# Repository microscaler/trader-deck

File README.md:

# PriceWhisperer Deck, rev A: case and board files

## 3D concept
The original concept is in [`concept/index.html`](concept/index.html). Open it in a browser to rotate it, tap keys, arm live orders and flip the FLATTEN guard. It loads three.js from a CDN, so it needs a network connection.

The concept is the design intent, not the built geometry. The case and board below differ from it in the ways listed under "What changed from the 3D concept".

## Layout
| Path | Contents |
|---|---|
| `src/` | Python that generates everything: `geom.py` (dimensions), `board.py` (footprints and nets), `route.py`, `fab.py`, `kicad.py`, `stl.py` |
| `gerber/` | Fabrication set: Gerbers, drill files, BOM |
| `stl/` | Printable case parts |
| `kicad/` | The routed board as a KiCad PCB, for KiCad's DRC |
| `concept/` | Interactive 3D concept page |
| `docs/` | Images used in this README |

`./build.sh` regenerates `gerber/`, `stl/`, `kicad/` and the previews from `src/` (`pip install -r requirements.txt` first). The output is deterministic: a rebuild reproduces the Gerbers byte for byte. Change a dimension in `src/geom.py` and both the case and the board follow.

Generated 2026-11-25. Nothing here has been printed, fabricated or powered. Treat it as a first prototype.

## What changed from the 3D concept
- Bottom row (ARM, CANCEL, FLATTEN) sits 6 mm below the other rows. The gap carries the guard hinge.
- FLATTEN is a 2u key shifted 2 mm right so the guard clears CANCEL.
- The display and dial sit on a raised deck, 5.5 mm above the switch plate.
- Outside size 94.4 x 122.4 mm, 20.6 mm tall at the deck, flat-bottomed. The optional rear riser tilts it about 4 degrees.

## Parts list
Links were found by web search on 2026-11-25 and not opened one by one. Check stock, price and shipping before ordering. Refs match `gerber/pw-deck-BOM.csv`.

### Electronics
| Qty | Part | Refs | Where to buy |
|---|---|---|---|
| 1 | Waveshare RP2040-Zero (no headers) | U1 | [Waveshare](https://waveshare.com/rp2040-zero.htm) |
| 15 | Kailh MX hot-swap socket, CPG151101S11 | SW1-SW15 | [KBDfans](https://kbdfans.com/collections/all/products/mechanical-keyboard-switches-kailh-pcb-socket), [Keyboardio, pack of 25](https://shop.keyboard.io/products/kailh-hotswap-sockets-for-mx-style-keyswitches-x-25), [Elecrow](https://www.elecrow.com/kailh-pcb-socket-sip-socket-hot-swappable-hot-plug-cpg151101s11-for-mechanical-keyboard.html) |
| 17 (buy 20) | SK6812MINI-E reverse-mount RGB LED, LCSC C5149201, sold in fives | LED1-LED15, LEDR1, LEDR2 | [LCSC](https://www.lcsc.com/product-detail/C5149201.html) |
| 16 | 1N4148W diode, SOD-123, LCSC C81598 | D1-D16 | [LCSC](https://www.lcsc.com/product-detail/C81598.html) |
| 2 (min 20) | 10 uF 25 V X5R capacitor, 0805, Samsung CL21A106KAYNNNE, LCSC C15850 | C1, C2 | [LCSC](https://www.lcsc.com/product-detail/C15850.html) |
| 1 | Alps EC11E15244G1 encoder: push switch, 30 detents, 6 mm D-shaft, 20 mm | ENC1 | [Octopart (all distributors)](https://octopart.com/part/alps/EC11E15244G1), [RS](https://ie.rs-online.com/web/p/mechanical-rotary-encoders/7295589), [Avnet](https://www.avnet.com/americas/product/alps-alpine/ec11e15244g1/evolve-169179) |
| 1 | 2.08 in 256x64 OLED module, SH1122, 7-pin SPI, 70.5 x 22.5 mm board | wired to J1 | [Open Electronics](https://oe2.open-electronics.org/?p=42977) |
| 1 strip | 2.54 mm 1x40 pin header, LCSC C2337: cut off 7 pins, or use 7 short wires | J1 | [LCSC](https://www.lcsc.com/product-detail/C2337.html) |
| 5 (fab minimum) | The PCB: 2 layers, 1.6 mm, upload `gerber/` | | [JLCPCB](https://jlcpcb.com/features/pcb-prototype), [PCBWay](https://www.pcbway.com/) |

### Mechanical
| Qty | Part | Where to buy |
|---|---|---|
| 15 (2 packs of 10) | MX-style switches, 3-pin or 5-pin, with an LED slot | [Gateron KS-9, 10 per pack (Apos)](https://apos.audio/collections/all/products/gateron-switches), [Gateron Blue, sold in tens (Mechboards)](https://www.mechboards.co.uk/products/gateron-blue), [price comparison (kbd.news)](https://kbd.news/switch/MX) |
| 14 (2 packs of 10) | 1u keycaps. Relegendable caps take a printed paper legend under a clear cover, which suits BUY, SELL, ARM and the rest | [Adafruit relegendable, 10 pack](https://www.adafruit.com/products/5039), [black relegendable DSA, set of 10 (MechanicalKeyboards)](https://mechanicalkeyboards.com/products/mk-1x1-dsa-relegendable-black-with-clear-top-set-of-10), [blank DSA singles (Signature Plastics)](https://spkeyboards.com/products/sp-dsa-1-space) |
| 1 | 2u keycap for FLATTEN, DSA profile, standard stabiliser mounts | [DSA 2u single (Signature Plastics)](https://spkeyboards.com/products/sp-dsa-2-space) |
| 1 | 2u plate-mount stabiliser, Cherry style | [KBDfans (sold as a set)](https://kbdfans.com/products/cherry-plate-mounted-stablizers) |
| 8 | M2 x 8 self-tapping screws, pan head | [Elecrow, bag of 200](https://elecrow.com/m2-screw-8mm.html) |
| 4 | Stick-on feet, 3M Bumpon SJ5003, 11.2 mm x 5 mm | [Buerklin, from 20](https://www.buerklin.com/en/self-adhesive-housing-bumper/p/20h175), [RS, bag of 56](https://uk.rs-online.com/web/p/anti-slip-pads/0236464) |
| 1 strip | Polyimide (Kapton) tape, 10 mm, under the RP2040-Zero | [Adafruit](https://www.adafruit.com/products/3057), [Olimex via DigiKey](https://www.digikey.be/en/products/detail/olimex-ltd/KAPTON-TAPE10MM/19204468) |
| 1 | USB-C to USB-C data cable, 1 m | [Pimoroni](https://shop.pimoroni.com/products/usb-c-to-usb-c-cable-1m-black) |
| about 75 g | 1.75 mm filament for the case, e.g. Prusament PLA Galaxy Black. A 42 mm offcut is the guard hinge pin | [Prusa](https://shop.prusa3d.com/prusament/711-prusament-pla-prusa-galaxy-black-1kg.html), [Galaxus](https://www.galaxus.de/en/s1/product/prusa-prusament-pla-pla-175-mm-1000-g-black-3d-printer-filament-23959778) |
| a few g | Clear filament for `dial_disc`, e.g. Prusament PETG Clear | [Prusa](https://prusa3d.com/product/prusament-petg-clear-1kg) |

Notes:
- The OLED must be the 70.5 x 22.5 mm board. The 72.5 x 27.4 mm breakout sold elsewhere does not fit the deck pocket.
- Octopart lists a last-time-buy date for the EC11E15244G1, so stock may thin out. Any EC11 with a push switch, a 6 mm D-shaft and 20 mm length fits the footprint and the knob.
- A plate-mount stabiliser is needed, not PCB-mount or screw-in: the board has no stabiliser holes.
- Relegendable 2u caps are rare, so FLATTEN gets a plain 2u cap. Signature Plastics sells singles from over-runs, so colours and stock vary.
- Some Prusa pages mark Galaxy Black PLA as discontinued in the non-NFC spool. Any 1.75 mm PLA or PETG works.
- The foot recesses in `bottom_shell` are 11.6 mm across to take the SJ5003.

## Printed parts (already in print orientation)
| File | Size mm | Volume cm3 |
|---|---|---|
| stl/pw-deck-bottom_shell.stl | 94.4 x 122.4 x 20.6 | 44.7 |
| stl/pw-deck-switch_plate.stl | 89.1 x 86.0 x 25.7 | 7.8 |
| stl/pw-deck-deck.stl | 89.1 x 32.2 x 10.2 | 5.0 |
| stl/pw-deck-flatten_guard.stl | 40.7 x 25.9 x 25.5 | 4.4 |
| stl/pw-deck-dial_disc.stl | 23.0 x 23.0 x 3.0 | 1.0 |
| stl/pw-deck-dial_knob.stl | 15.0 x 15.0 x 14.0 | 2.1 |
| stl/pw-deck-rear_riser_optional.stl | 80.0 x 14.0 x 8.0 | 8.4 |

- 0.4 mm nozzle, 0.2 mm layers. Only the bottom shell's USB opening bridges; no supports needed.
- Print dial_disc in clear or natural filament; it is the light ring under the knob.
- Guard hinge pin: a 42 mm length of 1.75 mm filament through the 2.1 mm holes.
- Screws: 8 x M2 x 8 self-tapping (5 through the plate, 3 through the deck) into 1.7 mm pilot holes.
- The switch plate is 1.5 mm with 14.1 mm cutouts. If switches are loose or tight, scale the cutouts, not the plate.
- Stack: floor 2.0, 6.5 gap, PCB 1.6, plate top 5.0 above the PCB, deck top 10.5 above the PCB.

## Board
- 2 layers, 88.6 x 116.6 mm, 1.6 mm. Track 0.30 mm (supply up to 0.60), clearance 0.20, vias 0.6/0.3 tented.
- Gerber X2 layers plus two Excellon files (PTH has two G85 slots for the encoder lugs; tell the fab if they ask).
- 17 LED windows and the outline are on Edge_Cuts.
- Everything except the encoder and wire header solders to the BOTTOM: hot-swap sockets, diodes, LEDs, 2 capacitors, controller.
- RP2040-Zero is soldered flat on the bottom, component side facing down, USB at the back edge. Put Kapton tape under it: the module has bare pads on its underside.
- Flash the module (or hold BOOT) before closing the case; its buttons face the floor.

### Controller pins
| RP2040-Zero pin | Net |
|---|---|
| GP0 | OLED_RES |
| GP1 | OLED_CS |
| GP2 | OLED_SCK |
| GP3 | OLED_MOSI |
| GP4 | OLED_DC |
| GP5 | COL0 |
| GP6 | COL1 |
| GP7 | ROW0 |
| GP8 | ROW1 |
| GP9 | ROW2 |
| GP10 | ROW3 |
| GP11 | COL2 |
| GP12 | COL3 |
| GP26 | ENC_B |
| GP27 | ENC_A |
| GP28 | LD0 |

GP13, GP14, GP15 and GP29 are free.

### Matrix (diodes: column to row, COL2ROW in QMK)
| | C0 | C1 | C2 | C3 |
|---|---|---|---|---|
| R0 | BUY MKT | BUY ASK | SELL BID | SELL MKT |
| R1 | HALF | DOUBLE | STOP BE | TRAIL |
| R2 | TICK- | TICK+ | TF- | TF+ |
| R3 | ARM | CANCEL | dial push | FLATTEN |

### LED chain (SK6812MINI-E, data from GP28)
LEDR1 > LEDR2 > LED4 > LED3 > LED2 > LED1 > LED5 > LED6 > LED7 > LED8 > LED12 > LED11 > LED10 > LED9 > LED13 > LED14 > LED15

LEDR1/LEDR2 are the dial ring. LED n sits under SW n.

### Display
2.08 in 256x64 SH1122 SPI module (70.5 x 22.5 mm board). It sticks to the underside of the deck and is wired to J1 (GND, VCC 3V3, SCL, SDA, RES, DC, CS, labelled on the board).

## Checks that were run
- Board: every net connected, no copper closer than 0.20 mm to another net, hole and edge clearances, all Gerbers parsed by a second library.
- Case: every part watertight; no overlap between shell, PCB, plate, deck, dial parts and guard, with the guard swept from closed to open.

## Check before you spend money
1. Display: the deck window assumes the glass is centred vertically on the module and sits 1 mm from the module's right-hand end. Measure yours; only the deck needs reprinting if it differs.
2. SK6812MINI-E pin order (1 VDD, 2 DOUT, 3 GND, 4 DIN) matches the open-source kbd footprint and a second public component listing. Still worth a glance at the datasheet for the exact LEDs you buy.
3. Stabiliser cutouts for FLATTEN use the common Cherry plate-mount dimensions from memory. Test-fit on a scrap print.
4. LEDs run from USB 5 V with 3.3 V data, which usually works but is outside the SK6812 spec. Cap brightness in firmware: 17 LEDs at full white exceeds 500 mA.
5. There is no schematic or KiCad project behind these Gerbers. The board was placed and routed by script, so run it through your fab's DFM viewer before ordering.
6. The guard clears keycaps up to about 20 mm above the plate (Cherry, OEM, DSA). SA profile is too tall.

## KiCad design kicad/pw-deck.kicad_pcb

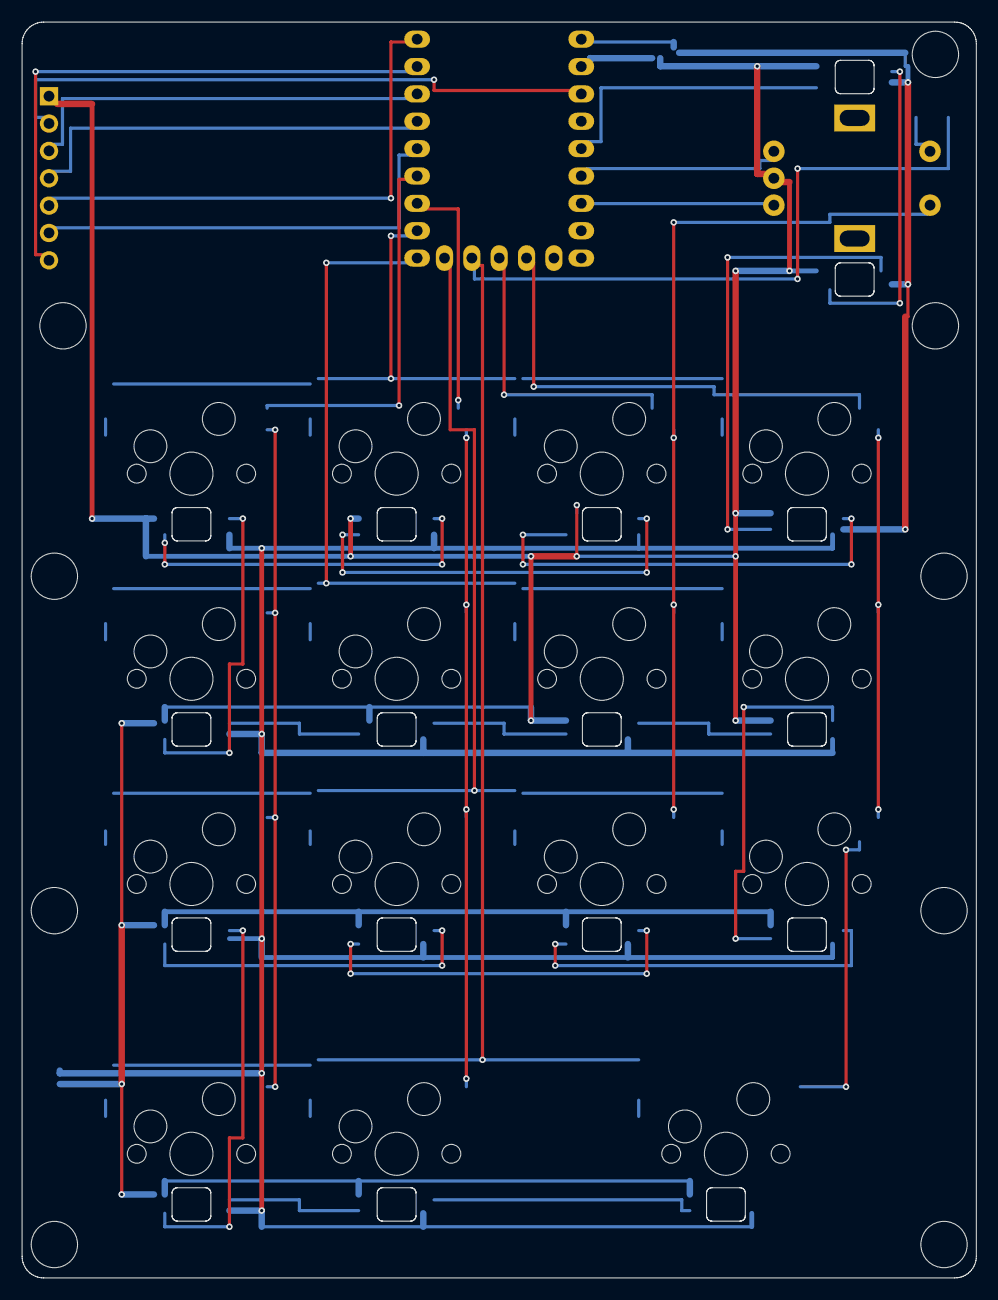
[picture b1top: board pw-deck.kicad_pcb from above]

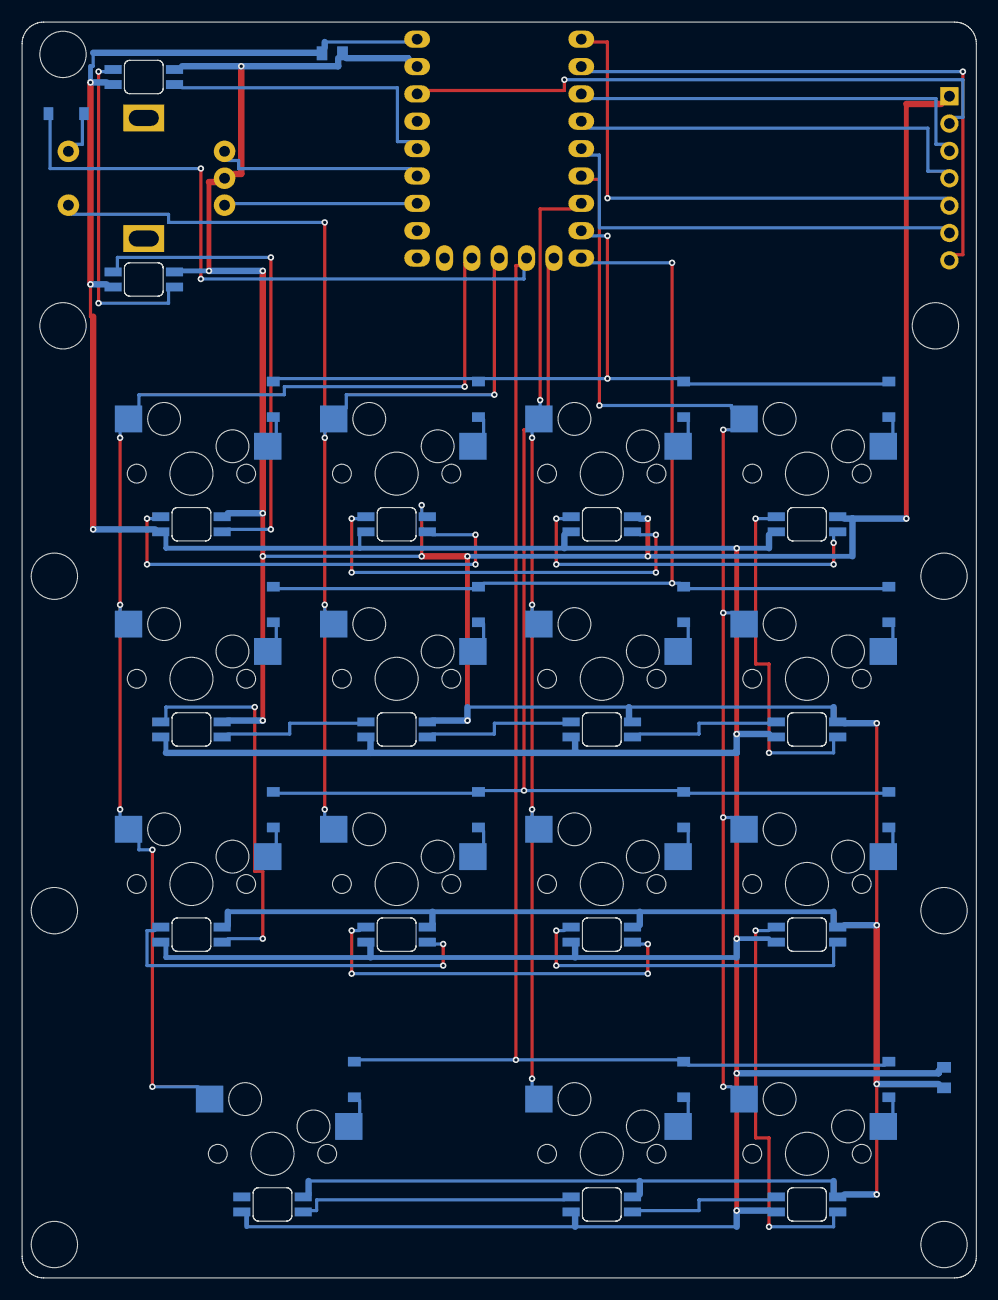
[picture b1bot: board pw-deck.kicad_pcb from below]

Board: 2 copper layers, 88.6 x 116.6 mm, 54 parts (51 on the bottom side), 51 nets.

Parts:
C1: 10uF 10V X5R; C1
C2: 10uF 10V X5R; C2
D1: 1N4148W; D1
D2: 1N4148W; D2
D3: 1N4148W; D3
D4: 1N4148W; D4
D5: 1N4148W; D5
D6: 1N4148W; D6
D7: 1N4148W; D7
D8: 1N4148W; D8
D9: 1N4148W; D9
D10: 1N4148W; D10
D11: 1N4148W; D11
D12: 1N4148W; D12
D13: 1N4148W; D13
D14: 1N4148W; D14
D15: 1N4148W; D15
D16: 1N4148W; D16
ENC1: EC11E push encoder, 20 mm D-shaft; ENC1
H1: holes
J1: 1x7 2.54 mm header or wires to OLED; J1
LED1: SK6812MINI-E; LED1
LED2: SK6812MINI-E; LED2
LED3: SK6812MINI-E; LED3
LED4: SK6812MINI-E; LED4
LED5: SK6812MINI-E; LED5
LED6: SK6812MINI-E; LED6
LED7: SK6812MINI-E; LED7
LED8: SK6812MINI-E; LED8
LED9: SK6812MINI-E; LED9
LED10: SK6812MINI-E; LED10
LED11: SK6812MINI-E; LED11
LED12: SK6812MINI-E; LED12
LED13: SK6812MINI-E; LED13
LED14: SK6812MINI-E; LED14
LED15: SK6812MINI-E; LED15
LEDR1: SK6812MINI-E; LEDR1
LEDR2: SK6812MINI-E; LEDR2
SW1: MX hot-swap socket (BUY MKT); SW1
SW2: MX hot-swap socket (BUY ASK); SW2
SW3: MX hot-swap socket (SELL BID); SW3
SW4: MX hot-swap socket (SELL MKT); SW4
SW5: MX hot-swap socket (HALF); SW5
SW6: MX hot-swap socket (DOUBLE); SW6
SW7: MX hot-swap socket (STOP BE); SW7
SW8: MX hot-swap socket (TRAIL); SW8
SW9: MX hot-swap socket (TICK-); SW9
SW10: MX hot-swap socket (TICK+); SW10
SW11: MX hot-swap socket (TF-); SW11
SW12: MX hot-swap socket (TF+); SW12
SW13: MX hot-swap socket (ARM); SW13
SW14: MX hot-swap socket (CANCEL); SW14
SW15: MX hot-swap socket (FLATTEN); SW15
U1: Waveshare RP2040-Zero (castellated, sold; U1

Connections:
3V3: J1.VCC, U1.3V3
5V: C1.2, C2.1, LED1.1, LED2.1, LED3.1, LED4.1, LED5.1, LED6.1, LED7.1, LED8.1, LED9.1, LED10.1, LED11.1, LED12.1, LED13.1, LED14.1, LED15.1, LEDR1.1, LEDR2.1, U1.5V
COL0: SW1.2, SW5.2, SW9.2, SW13.2, U1.GP5
COL1: SW2.2, SW6.2, SW10.2, SW14.2, U1.GP6
COL2: ENC1.S1, SW3.2, SW7.2, SW11.2, U1.GP11
COL3: SW4.2, SW8.2, SW12.2, SW15.2, U1.GP12
ENC_A: ENC1.A, U1.GP27
ENC_B: ENC1.B, U1.GP26
GND: C1.1, C2.2, ENC1.C, J1.GND, LED1.3, LED2.3, LED3.3, LED4.3, LED5.3, LED6.3, LED7.3, LED8.3, LED9.3, LED10.3, LED11.3, LED12.3, LED13.3, LED14.3, LED15.3, LEDR1.3, LEDR2.3, U1.GND
LD0: LEDR1.4, U1.GP28
LD1: LEDR1.2, LEDR2.4
LD2: LED4.4, LEDR2.2
LD3: LED3.4, LED4.2
LD4: LED2.4, LED3.2
LD5: LED1.4, LED2.2
LD6: LED1.2, LED5.4
LD7: LED5.2, LED6.4
LD8: LED6.2, LED7.4
LD9: LED7.2, LED8.4
LD10: LED8.2, LED12.4
LD11: LED11.4, LED12.2
LD12: LED10.4, LED11.2
LD13: LED9.4, LED10.2
LD14: LED9.2, LED13.4
LD15: LED13.2, LED14.4
LD16: LED14.2, LED15.4
N_ENCSW: D16.A, ENC1.S2
N_SW1: D1.A, SW1.1
N_SW2: D2.A, SW2.1
N_SW3: D3.A, SW3.1
N_SW4: D4.A, SW4.1
N_SW5: D5.A, SW5.1
N_SW6: D6.A, SW6.1
N_SW7: D7.A, SW7.1
N_SW8: D8.A, SW8.1
N_SW9: D9.A, SW9.1
N_SW10: D10.A, SW10.1
N_SW11: D11.A, SW11.1
N_SW12: D12.A, SW12.1
N_SW13: D13.A, SW13.1
N_SW14: D14.A, SW14.1
N_SW15: D15.A, SW15.1
OLED_CS: J1.CS, U1.GP1
OLED_DC: J1.DC, U1.GP4
OLED_MOSI: J1.SDA, U1.GP3
OLED_RES: J1.RES, U1.GP0
OLED_SCK: J1.SCL, U1.GP2
ROW0: D1.K, D2.K, D3.K, D4.K, U1.GP7
ROW1: D5.K, D6.K, D7.K, D8.K, U1.GP8
ROW2: D9.K, D10.K, D11.K, D12.K, U1.GP9
ROW3: D13.K, D14.K, D15.K, D16.K, U1.GP10

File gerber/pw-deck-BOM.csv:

Ref,Value,Footprint,Side,X mm,Y mm
LEDR1,SK6812MINI-E,reverse-mount RGB LED,bottom,33.000,65.400
LEDR2,SK6812MINI-E,reverse-mount RGB LED,bottom,33.000,46.600
SW1,MX hot-swap socket (BUY MKT),Kailh CPG151101S11,bottom,-28.575,28.575
D1,1N4148W,SOD-123,bottom,-36.175,35.475
LED1,SK6812MINI-E,reverse-mount RGB LED,bottom,-28.575,23.875
SW2,MX hot-swap socket (BUY ASK),Kailh CPG151101S11,bottom,-9.525,28.575
D2,1N4148W,SOD-123,bottom,-17.125,35.475
LED2,SK6812MINI-E,reverse-mount RGB LED,bottom,-9.525,23.875
SW3,MX hot-swap socket (SELL BID),Kailh CPG151101S11,bottom,9.525,28.575
D3,1N4148W,SOD-123,bottom,1.925,35.475
LED3,SK6812MINI-E,reverse-mount RGB LED,bottom,9.525,23.875
SW4,MX hot-swap socket (SELL MKT),Kailh CPG151101S11,bottom,28.575,28.575
D4,1N4148W,SOD-123,bottom,20.975,35.475
LED4,SK6812MINI-E,reverse-mount RGB LED,bottom,28.575,23.875
SW5,MX hot-swap socket (HALF),Kailh CPG151101S11,bottom,-28.575,9.525
D5,1N4148W,SOD-123,bottom,-36.175,16.425
LED5,SK6812MINI-E,reverse-mount RGB LED,bottom,-28.575,4.825
SW6,MX hot-swap socket (DOUBLE),Kailh CPG151101S11,bottom,-9.525,9.525
D6,1N4148W,SOD-123,bottom,-17.125,16.425
LED6,SK6812MINI-E,reverse-mount RGB LED,bottom,-9.525,4.825
SW7,MX hot-swap socket (STOP BE),Kailh CPG151101S11,bottom,9.525,9.525
D7,1N4148W,SOD-123,bottom,1.925,16.425
LED7,SK6812MINI-E,reverse-mount RGB LED,bottom,9.525,4.825
SW8,MX hot-swap socket (TRAIL),Kailh CPG151101S11,bottom,28.575,9.525
D8,1N4148W,SOD-123,bottom,20.975,16.425
LED8,SK6812MINI-E,reverse-mount RGB LED,bottom,28.575,4.825
SW9,MX hot-swap socket (TICK-),Kailh CPG151101S11,bottom,-28.575,-9.525
D9,1N4148W,SOD-123,bottom,-36.175,-2.625
LED9,SK6812MINI-E,reverse-mount RGB LED,bottom,-28.575,-14.225
SW10,MX hot-swap socket (TICK+),Kailh CPG151101S11,bottom,-9.525,-9.525
D10,1N4148W,SOD-123,bottom,-17.125,-2.625
LED10,SK6812MINI-E,reverse-mount RGB LED,bottom,-9.525,-14.225
SW11,MX hot-swap socket (TF-),Kailh CPG151101S11,bottom,9.525,-9.525
D11,1N4148W,SOD-123,bottom,1.925,-2.625
LED11,SK6812MINI-E,reverse-mount RGB LED,bottom,9.525,-14.225
SW12,MX hot-swap socket (TF+),Kailh CPG151101S11,bottom,28.575,-9.525
D12,1N4148W,SOD-123,bottom,20.975,-2.625
LED12,SK6812MINI-E,reverse-mount RGB LED,bottom,28.575,-14.225
SW13,MX hot-swap socket (ARM),Kailh CPG151101S11,bottom,-28.575,-34.575
D13,1N4148W,SOD-123,bottom,-36.175,-27.675
LED13,SK6812MINI-E,reverse-mount RGB LED,bottom,-28.575,-39.275
SW14,MX hot-swap socket (CANCEL),Kailh CPG151101S11,bottom,-9.525,-34.575
D14,1N4148W,SOD-123,bottom,-17.125,-27.675
LED14,SK6812MINI-E,reverse-mount RGB LED,bottom,-9.525,-39.275
SW15,MX hot-swap socket (FLATTEN),Kailh CPG151101S11,bottom,21.050,-34.575
D15,1N4148W,SOD-123,bottom,13.450,-27.675
LED15,SK6812MINI-E,reverse-mount RGB LED,bottom,21.050,-39.275
ENC1,"EC11E push encoder, 20 mm D-shaft",Alps EC11E,top,33.000,56.000
D16,1N4148W,SOD-123,bottom,40.200,62.000
U1,"Waveshare RP2040-Zero (castellated, soldered flat on the bottom)",RP2040-Zero,bottom,0.000,58.750
J1,1x7 2.54 mm header or wires to OLED,PinHeader 1x07,top,-41.800,56.000
C1,10uF 10V X5R,0805,bottom,15.500,67.600
C2,10uF 10V X5R,0805,bottom,-41.300,-27.500
